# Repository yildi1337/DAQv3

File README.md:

# DAQv3
A Dual-Channel, Low Noise, Modular, 100 kHz Bandwidth, 24-Bit Data Acquisition (DAQ) Device / FFT Signal Analyzer

# Table of Contents

- **[Introduction](#introduction)**
- **[CAD Model](#cad-model)**
- **[Modules](#modules)**
  - [AnalogConversion_v1](#AnalogConversion_v1)
  - [AnalogConversion_v2](#AnalogConversion_v2)
  - [AnalogConversion_v3](#AnalogConversion_v3)
  - [Backplane_v1](#Backplane_v1)
  - [DigitalBackend_v1](#DigitalBackend_v1)
  - [PowerSupply_5V_v1](#PowerSupply_5V_v1)
  - [PowerSupply_5V_v2](#PowerSupply_5V_v2)
  - [PowerSupply_12V_v1](#PowerSupply_12V_v1)
  - [PowerSupply_12V_v2](#PowerSupply_12V_v2)
  - [USBConnectors_v1](#USBConnectors_v1)
- **[Firmware](#firmware)**
- **[USB Driver](#usb-driver)**
- **[Debug and Control Interface](#debug-and-control-interface)**
- **[Measurement Results](#measurement-results)**
  - [Linear Power Supply vs. Switched-Mode Power Supply](#linear-power-supply-vs-switched-mode-power-supply)
  - [Differential Input Module (AnalogConversion_v3)](#differential-input-module-analogconversion_v3)

# Introduction

Work in progress ...

# Rack
+ [Card Rail](https://it.rs-online.com/web/p/montanti-rack/2457848)
+ [Front Pannel Large](https://it.rs-online.com/web/p/accessori-per-contenitori/2879769) (10 HP)
+ [Front Pannel Small](https://us.rs-online.com/product/nvent-schroff/20848664/70294016/)  (4 HP)
+ [Case](https://it.rs-online.com/web/p/contenitori-e-scatole-rack/2550700?searchId=d65bfb2c-882b-444f-99ba-9c0d112e01d9&gb=s)  (42 HP)
+ [IEC Connector](https://it.rs-online.com/web/p/filtri-iec/8703669)

# CAD Model

The complete CAD model can be downloaded <a href="https://github.com/yildi1337/DAQv3/tree/main/cad_complete/inventor">here</a> (Autodesk Inventor 2023 files) including all <a href="#modules">modules</a> and the case.

# Modules

## AnalogConversion_v1

- [Schematics (PDF)](https://github.com/yildi1337/DAQv3/blob/main/schematics/AnalogConversion_v1_Schematics.pdf)
- [Schematics (Eagle)](https://github.com/yildi1337/DAQv3/blob/main/eagle/AnalogConversion_v1.sch)
- [Board (Eagle)](https://github.com/yildi1337/DAQv3/blob/main/eagle/AnalogConversion_v1.brd)
- [Gerber Files](https://github.com/yildi1337/DAQv3/blob/main/pcb_gerber/AnalogConversion_v1_2022-03-20.zip)
- [3D Step File](https://github.com/yildi1337/DAQv3/blob/main/cad_modules_step/AnalogConversion_v1.step)
- [Bill of Materials](https://github.com/yildi1337/DAQv3/blob/main/pcb_bom/BOM_AnalogConversion_v1.txt)

## AnalogConversion_v2

- [Schematics (PDF)](https://github.com/yildi1337/DAQv3/blob/main/schematics/AnalogConversion_v2_Schematics.pdf)
- [Schematics (Eagle)](https://github.com/yildi1337/DAQv3/blob/main/eagle/AnalogConversion_v2.sch)
- [Board (Eagle)](https://github.com/yildi1337/DAQv3/blob/main/eagle/AnalogConversion_v2.brd)
- [Gerber Files](https://github.com/yildi1337/DAQv3/blob/main/pcb_gerber/AnalogConversion_v2_2022-05-25.zip)
- [3D Step File](https://github.com/yildi1337/DAQv3/blob/main/cad_modules_step/AnalogConversion_v2.step)
- [Bill of Materials](https://github.com/yildi1337/DAQv3/blob/main/pcb_bom/BOM_AnalogConversion_v2.txt)

## AnalogConversion_v3

- [Schematics (PDF)](https://github.com/yildi1337/DAQv3/blob/main/schematics/AnalogConversion_v3_Schematics.pdf)
- [Schematics (Eagle)](https://github.com/yildi1337/DAQv3/blob/main/eagle/AnalogConversion_v3.sch)
- [Board (Eagle)](https://github.com/yildi1337/DAQv3/blob/main/eagle/AnalogConversion_v3.brd)
- [Gerber Files](https://github.com/yildi1337/DAQv3/blob/main/pcb_gerber/AnalogConversion_v3_2022-07-25.zip)
- [3D Step File](https://github.com/yildi1337/DAQv3/blob/main/cad_modules_step/AnalogConversion_v3.step)
- [Bill of Materials](https://github.com/yildi1337/DAQv3/blob/main/pcb_bom/BOM_AnalogConversion_v3.txt)

## Backplane_v1

- [Schematics (PDF)](https://github.com/yildi1337/DAQv3/blob/main/schematics/Backplane_v1_Schematics.pdf)
- [Schematics (Eagle)](https://github.com/yildi1337/DAQv3/blob/main/eagle/Backplane_v1.sch)
- [Board (Eagle)](https://github.com/yildi1337/DAQv3/blob/main/eagle/Backplane_v1.brd)
- [Gerber Files](https://github.com/yildi1337/DAQv3/blob/main/pcb_gerber/Backplane_v1_2022-03-20.zip)
- [3D Step File](https://github.com/yildi1337/DAQv3/blob/main/cad_modules_step/Backplane_v1.step)
- [Bill of Materials](https://github.com/yildi1337/DAQv3/blob/main/pcb_bom/BOM_Backplane_v1.txt)

## DigitalBackend_v1

- [Schematics (PDF)](https://github.com/yildi1337/DAQv3/blob/main/schematics/DigitalBackend_v1_Schematics.pdf)
- [Schematics (Eagle)](https://github.com/yildi1337/DAQv3/blob/main/eagle/DigitalBackend_v1.sch)
- [Board (Eagle)](https://github.com/yildi1337/DAQv3/blob/main/eagle/DigitalBackend_v1.brd)
- [Gerber Files](https://github.com/yildi1337/DAQv3/blob/main/pcb_gerber/DigitalBackend_v1_2022-03-20.zip)
- [3D Step File](https://github.com/yildi1337/DAQv3/blob/main/cad_modules_step/DigitalBackend_v1.step)
- [Bill of Materials](https://github.com/yildi1337/DAQv3/blob/main/pcb_bom/BOM_DigitalBackend_v1.txt)

## PowerSupply_12V_v1

- [Schematics (PDF)](https://github.com/yildi1337/DAQv3/blob/main/schematics/PowerSupply_12V_v1_Schematics.pdf)
- [Schematics (Eagle)](https://github.com/yildi1337/DAQv3/blob/main/eagle/PowerSupply_12V_v1.sch)
- [Board (Eagle)](https://github.com/yildi1337/DAQv3/blob/main/eagle/PowerSupply_12V_v1.brd)
- [Gerber Files](https://github.com/yildi1337/DAQv3/blob/main/pcb_gerber/PowerSupply_12V_v1_2022-03-20.zip)
- [3D Step File](https://github.com/yildi1337/DAQv3/blob/main/cad_modules_step/PowerSupply_12V_v1.step)
- [Bill of Materials](https://github.com/yildi1337/DAQv3/blob/main/pcb_bom/BOM_PowerSupply_12V_v1.txt)

## PowerSupply_12V_v2

- [Schematics (PDF)](https://github.com/yildi1337/DAQv3/blob/main/schematics/PowerSupply_12V_v2_Schematics.pdf)
- [Schematics (Eagle)](https://github.com/yildi1337/DAQv3/blob/main/eagle/PowerSupply_12V_v2.sch)
- [Board (Eagle)](https://github.com/yildi1337/DAQv3/blob/main/eagle/PowerSupply_12V_v2.brd)
- [Gerber Files](https://github.com/yildi1337/DAQv3/blob/main/pcb_gerber/PowerSupply_12V_v2_2022-05-25.zip)
- [3D Step File](https://github.com/yildi1337/DAQv3/blob/main/cad_modules_step/PowerSupply_12V_v2.step)
- [Bill of Materials](https://github.com/yildi1337/DAQv3/blob/main/pcb_bom/BOM_PowerSupply_12V_v2.txt)

## PowerSupply_5V_v1

- [Schematics (PDF)](https://github.com/yildi1337/DAQv3/blob/main/schematics/PowerSupply_5V_v1_Schematics.pdf)
- [Schematics (Eagle)](https://github.com/yildi1337/DAQv3/blob/main/eagle/PowerSupply_5V_v1.sch)
- [Board (Eagle)](https://github.com/yildi1337/DAQv3/blob/main/eagle/PowerSupply_5V_v1.brd)
- [Gerber Files](https://github.com/yildi1337/DAQv3/blob/main/pcb_gerber/PowerSupply_5V_v1_2022-03-20.zip)
- [3D Step File](https://github.com/yildi1337/DAQv3/blob/main/cad_modules_step/PowerSupply_5V_v1.step)
- [Bill of Materials](https://github.com/yildi1337/DAQv3/blob/main/pcb_bom/BOM_PowerSupply_5V_v1.txt)

## PowerSupply_5V_v2

- [Schematics (PDF)](https://github.com/yildi1337/DAQv3/blob/main/schematics/PowerSupply_5V_v2_Schematics.pdf)
- [Schematics (Eagle)](https://github.com/yildi1337/DAQv3/blob/main/eagle/PowerSupply_5V_v2.sch)
- [Board (Eagle)](https://github.com/yildi1337/DAQv3/blob/main/eagle/PowerSupply_5V_v2.brd)
- [Gerber Files](https://github.com/yildi1337/DAQv3/blob/main/pcb_gerber/PowerSupply_5V_v2_2022-05-25.zip)
- [3D Step File](https://github.com/yildi1337/DAQv3/blob/main/cad_modules_step/PowerSupply_5V_v2.step)
- [Bill of Materials](https://github.com/yildi1337/DAQv3/blob/main/pcb_bom/BOM_PowerSupply_5V_v2.txt)

## USBConnectors_v1

- [Schematics (PDF)](https://github.com/yildi1337/DAQv3/blob/main/schematics/USBConnectors_v1_Schematics.pdf)
- [Schematics (Eagle)](https://github.com/yildi1337/DAQv3/blob/main/eagle/USBConnectors_v1.sch)
- [Board (Eagle)](https://github.com/yildi1337/DAQv3/blob/main/eagle/USBConnectors_v1.brd)
- [Gerber Files](https://github.com/yildi1337/DAQv3/blob/main/pcb_gerber/USBConnectors_v1_2022-03-14.zip)
- [3D Step File](https://github.com/yildi1337/DAQv3/blob/main/cad_modules_step/USBConnectors_v1.step)
- [Bill of Materials](https://github.com/yildi1337/DAQv3/blob/main/pcb_bom/BOM_USBConnectors_v1.txt)

# Firmware

The firmware running on the STM32H753ZIT6 is mainly written in ANSI C and has been developed in <a href="https://www.st.com/en/development-tools/stm32cubeide.html">STM32CubeIDE</a> version 1.10.1 utilizing the official <a href="https://github.com/STMicroelectronics/stm32h7xx_hal_driver">STM32H7xx_HAL_Driver</a>. Among others, the firmware performs the following tasks:

- Configuration of the ADC AD7768 (on module <a href="#AnalogConversion_v3">AnalogConversion_v3</a>) via SPI (SPI_3).
- Reception of sampled data from the ADC AD7768 via SPI (SPI_2) and DMA (DMA1_Stream0).
- Transmission of sampled data from the ADC AD7768 via USB 2.0 Hi-Speed to the PC utilizing ULPI interface and an additional Hi-Speed USB PHY (USB3300).
- Handling USART connection (USART_1, via FT232RL chip on <a href="#USBConnectors_v1">USBConnectors_v1</a>) for debug purposes and for exchanging control/status commands with the PC.
- Controlling I2C bus (I2C_4) for controlling I/O expander TCA9534A (e.g. on module <a href="#AnalogConversion_v3">AnalogConversion_v3</a>) which, in turn, drives a relay driver (MAX4820) on the same module.
- Controlling front LEDs (on module <a href="#DigitalBackend_v1">DigitalBackend_v1</a>).

The complete source code can be found <a href="https://github.com/yildi1337/DAQv3/tree/main/firmware">here</a>.

# USB Driver

Two USB drivers are needed for operating the DAQ v3:

- For the reception of the sampled data from the ADC NI-VISA is utilized. The driver matching the hardware of this project has been generated with the NI-VISA Driver Wizard an can be downloaded <a href="https://github.com/yildi1337/DAQv3/tree/main/usb_driver/ni-visa">here</a>.
- To use the USB debug interface only the official USB serial driver from FTDI is required, which can be downloaded <a href="https://github.com/yildi1337/DAQv3/tree/main/usb_driver/ftdi">here</a>.

# Debug and Control Interface

Tool for graphical display of status information and for controlling the hardware via the virtual serial interface (second USB-B port). The python source code and a binary (only tested on x64 Microsoft Windows 10) can be downloaded <a href="https://github.com/yildi1337/DAQv3/tree/main/debug_interface">here</a>. 

# Measurement Results

## Linear Power Supply vs. Switched-Mode Power Supply

Noise measurements (60 seconds) were performed while powering the electronics with the power supplies of versions v1 and v2, where the abbreviations PS and ACNV in the titles refer to the power supply and analog conversion modules.

The two linear power supply modules of version v1 both operate with transformers. This resulted in heavy magnetic interference in the form of the mains frequency and multiples thereof.

The two power supply modules of version v2 both operate with AC/DC power modules (<a href="https://www.tracopower.com/de/deu/model/tmlm-20105">TMLM 20105</a>, <a href="https://www.tracopower.com/de/deu/model/tmlm-20115">TMLM 20115</a>) from Traco Power. Their switching frequencies are around 132 +/- 8 kHz and thus above the useful range of 0 - 100 kHz (Nyquist frequency is 128 kHz).

## Differential Input Module (AnalogConversion_v3)

The investigated setup consists of the modules:

- <a href="#Backplane_v1">Backplane_v1</a>
- <a href="#PowerSupply_5V_v2">PowerSupply_5V_v2</a>
- <a href="#PowerSupply_12V_v2">PowerSupply_12V_v2</a>
- <a href="#AnalogConversion_v3">AnalogConversion_v3</a>
- <a href="#DigitalBackend_v1">DigitalBackend_v1</a>
- <a href="#USBConnectors_v1">USBConnectors_v1</a>

### Mains Interference and Grounding

The two differential inputs of each channel were connected via <a href="https://www.mouser.de/ProductDetail/Amphenol-RF/132360?qs=V8V9vCxO5JtDrelx3RqrVA%3D%3D">50 Ohm SMA resistors</a> with AGND (SHIELD connected via R6 = 0 Ohm with AGND, <a href="https://github.com/yildi1337/DAQv3/blob/main/schematics/AnalogConversion_v3_Schematics.pdf">see schematics</a>).

Obviously, the lowest interference occurs in grounded mode and when GND of the backplane is directly connected to the chassis/the protective earth connector of the power entry module (first plot).

### Input Noise of Differential Opamp Driver and ADC

The measurement result from above is essential for the further development of the preamplifier. The gain of the preamplifier must be high enough to be able to neglect the noise from the opamp driver (ADA4945-1) and ADC (AD7768-4) determined here. A useful model for describing the power spectral density of the voltage noise $PSD(f)$ (in units of $\mathrm{V}^2/\mathrm{Hz}$) is the polynomial law 
$$\mathrm{PSD}(f) = \mathrm{LSD}^2(f) = \sum_{i=-1}^{0} b_i f^i$$ 
where $i=0$ and $i=-1$ refer to white noise and $1/f$ flicker noise, respectively, and $\mathrm{LSD}(f)$ referes to the linear spectrum density (in units of $\mathrm{V}/\sqrt{\mathrm{Hz}}$). For this measurement, values of
- $b_{-1} = 1.3 \cdot 10^{-13}~\mathrm{V}^2$
- $b_0 = {1.3 \cdot 10^{-15}~\mathrm{V}^2/\mathrm{Hz}}$
were found.

This results in a $1/f$ corner frequency of $f_{\mathrm{c}} = b_{-1}/b_0 = 100~\mathrm{Hz}$. The white voltage noise density is equal to $\sqrt{b_0} = 36~\mathrm{nV}/\sqrt{\mathrm{Hz}}$. Based on the two time domain noise signals RMS noise values of $13.2~\mu\mathrm{V}$ (channel 1) and $13.5~\mu\mathrm{V}$ (channel 2) were determined after substracting the DC offsets of $-6.5~\mathrm{mV}$ and $-1.8~\mathrm{mV}$.

The measured RMS noise values are in good agreement with the value of $11.58~\mu\mathrm{V}$ given in the datasheet (for the ADC only).

In addition, for $V_{\mathrm{ref}} = 5~\mathrm{V}$, the dynamic range of the utilized combination of opamp driver and ADC is better than 

$$\mathrm{DR} = 20 \cdot \log_{10}\left(\frac{2 \cdot V_{\mathrm{ref}}}{\sqrt{2} \cdot \mathrm{RMS}\ \mathrm{noise}}\right)~\mathrm{dB} = 114\ \mathrm{dB}$$ 

### ADC RAW Data for Several Input Configurations

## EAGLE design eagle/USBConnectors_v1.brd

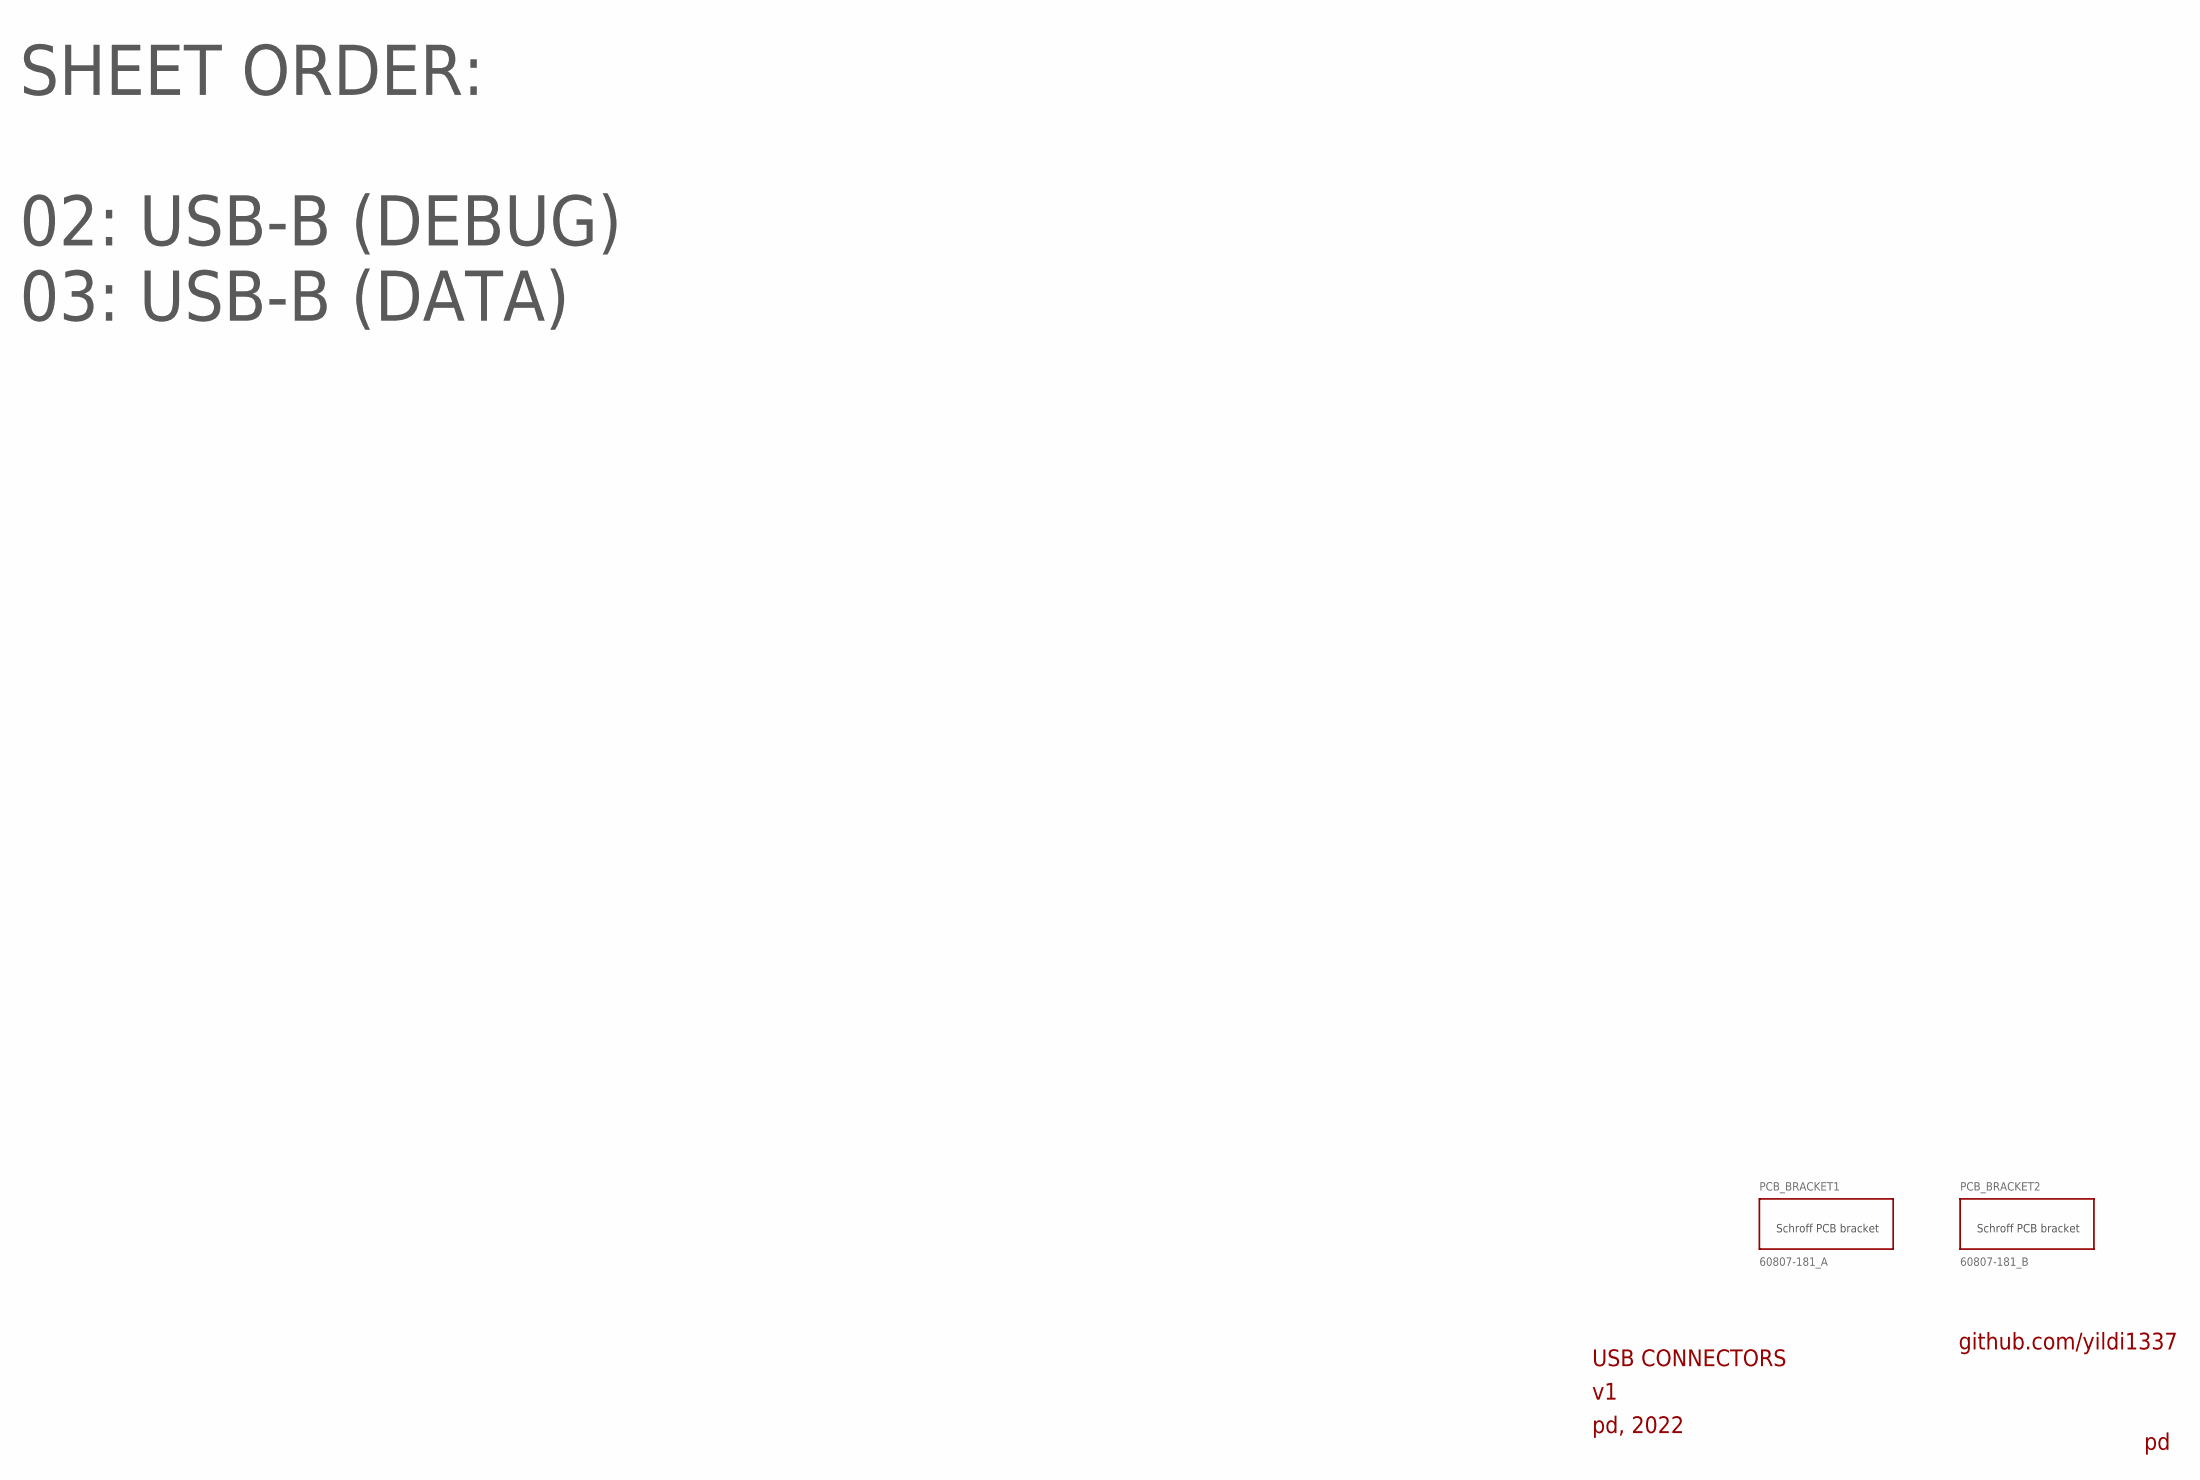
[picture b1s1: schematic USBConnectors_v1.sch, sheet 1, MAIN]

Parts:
PCB_BRACKET1: 60807-181_A
PCB_BRACKET2: 60807-181_B

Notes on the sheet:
USB CONNECTORS
pd, 2022
github.com/yildi1337
SHEET ORDER: 02: USB-B (DEBUG) 03: USB-B (DATA)

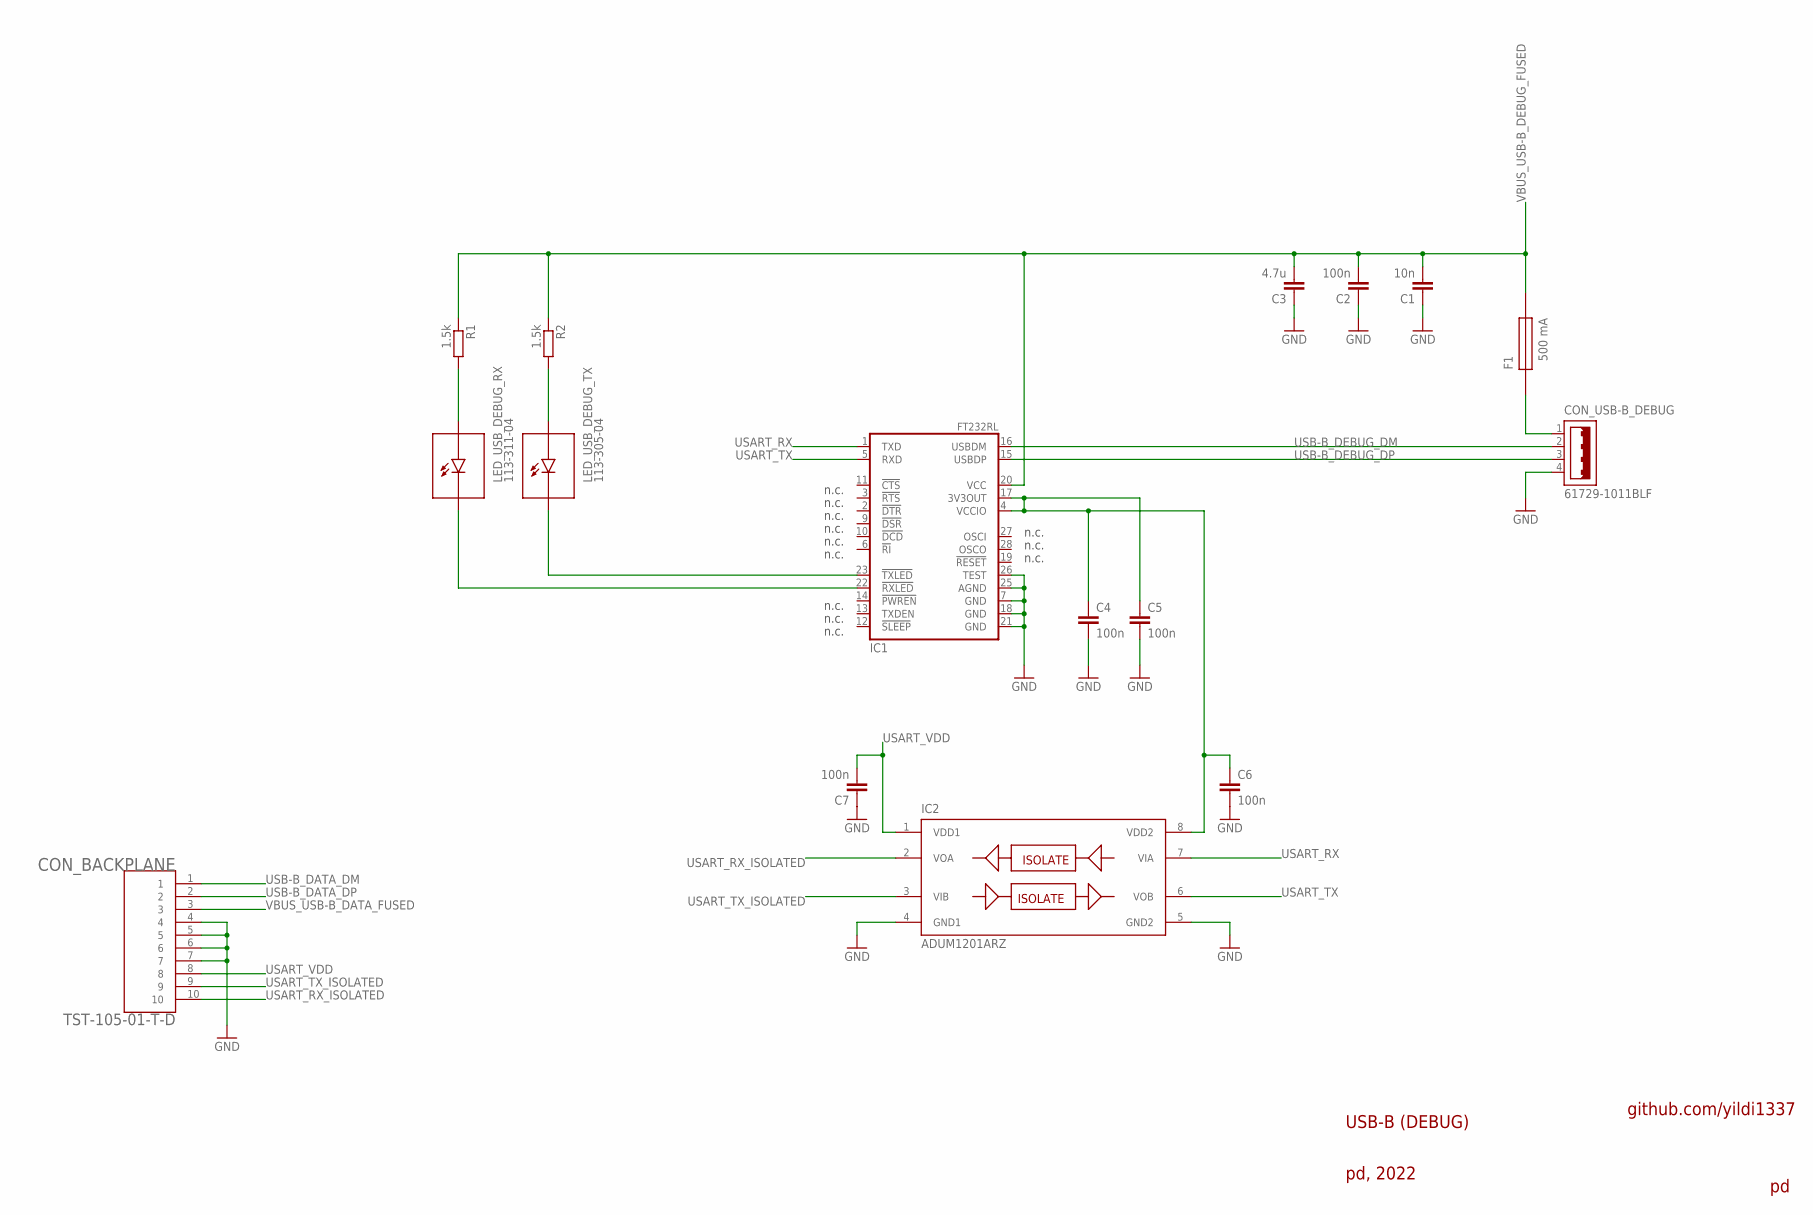
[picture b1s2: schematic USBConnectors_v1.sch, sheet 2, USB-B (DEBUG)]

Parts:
C1: 10n; C0603
C2, C4, C5, C6, C7: 100n; C0603
C3: 4.7u; C0603
CON_BACKPLANE: TST-105-01-T-D
CON_USB-B_DEBUG: 61729-1011BLF
F1: 500 mA; LITTELFUSE_466_SERIES
IC1: FT232RL
IC2: ADUM1201ARZ; SO8
LED_USB_DEBUG_RX: 113-311-04
LED_USB_DEBUG_TX: 113-305-04
R1, R2: 1.5k; R0603

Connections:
GND: C1.2, C2.1, C3.1, C4.2, C5.2, C6.2, C7.1, CON_BACKPLANE.4, CON_BACKPLANE.5, CON_BACKPLANE.6, CON_BACKPLANE.7, CON_USB-B_DEBUG.4, IC1.7 (GND), IC1.18 (GND), IC1.21 (GND), IC1.25 (AGND), IC1.26 (TEST), IC2.4 (GND1), IC2.5 (GND2); also elsewhere on the board
unnamed: CON_USB-B_DEBUG.1, F1.1
unnamed: LED_USB_DEBUG_RX.+ (A), R1.2
unnamed: LED_USB_DEBUG_TX.+ (A), R2.2
unnamed: C4.1, C5.1, C6.1, IC1.4 (VCCIO), IC1.17 (3V3OUT), IC2.8 (VDD2)
unnamed: IC1.22 (!RXLED), LED_USB_DEBUG_RX.- (C)
unnamed: IC1.23 (!TXLED), LED_USB_DEBUG_TX.- (C)
USART_RX: IC1.1 (TXD), IC2.7 (VIA)
USART_RX_ISOLATED: CON_BACKPLANE.10, IC2.2 (VOA)
USART_TX: IC1.5 (RXD), IC2.6 (VOB)
USART_TX_ISOLATED: CON_BACKPLANE.9, IC2.3 (VIB)
USART_VDD: C7.2, CON_BACKPLANE.8, IC2.1 (VDD1)
USB-B_DATA_DM: CON_BACKPLANE.1; also elsewhere on the board
USB-B_DATA_DP: CON_BACKPLANE.2; also elsewhere on the board
USB-B_DEBUG_DM: CON_USB-B_DEBUG.2, IC1.16 (USBDM)
USB-B_DEBUG_DP: CON_USB-B_DEBUG.3, IC1.15 (USBDP)
VBUS_USB-B_DATA_FUSED: CON_BACKPLANE.3; also elsewhere on the board
VBUS_USB-B_DEBUG_FUSED: C1.1, C2.2, C3.2, F1.2, IC1.20 (VCC), R1.1, R2.1

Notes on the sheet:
n.c.
USB-B (DEBUG)
pd, 2022
github.com/yildi1337

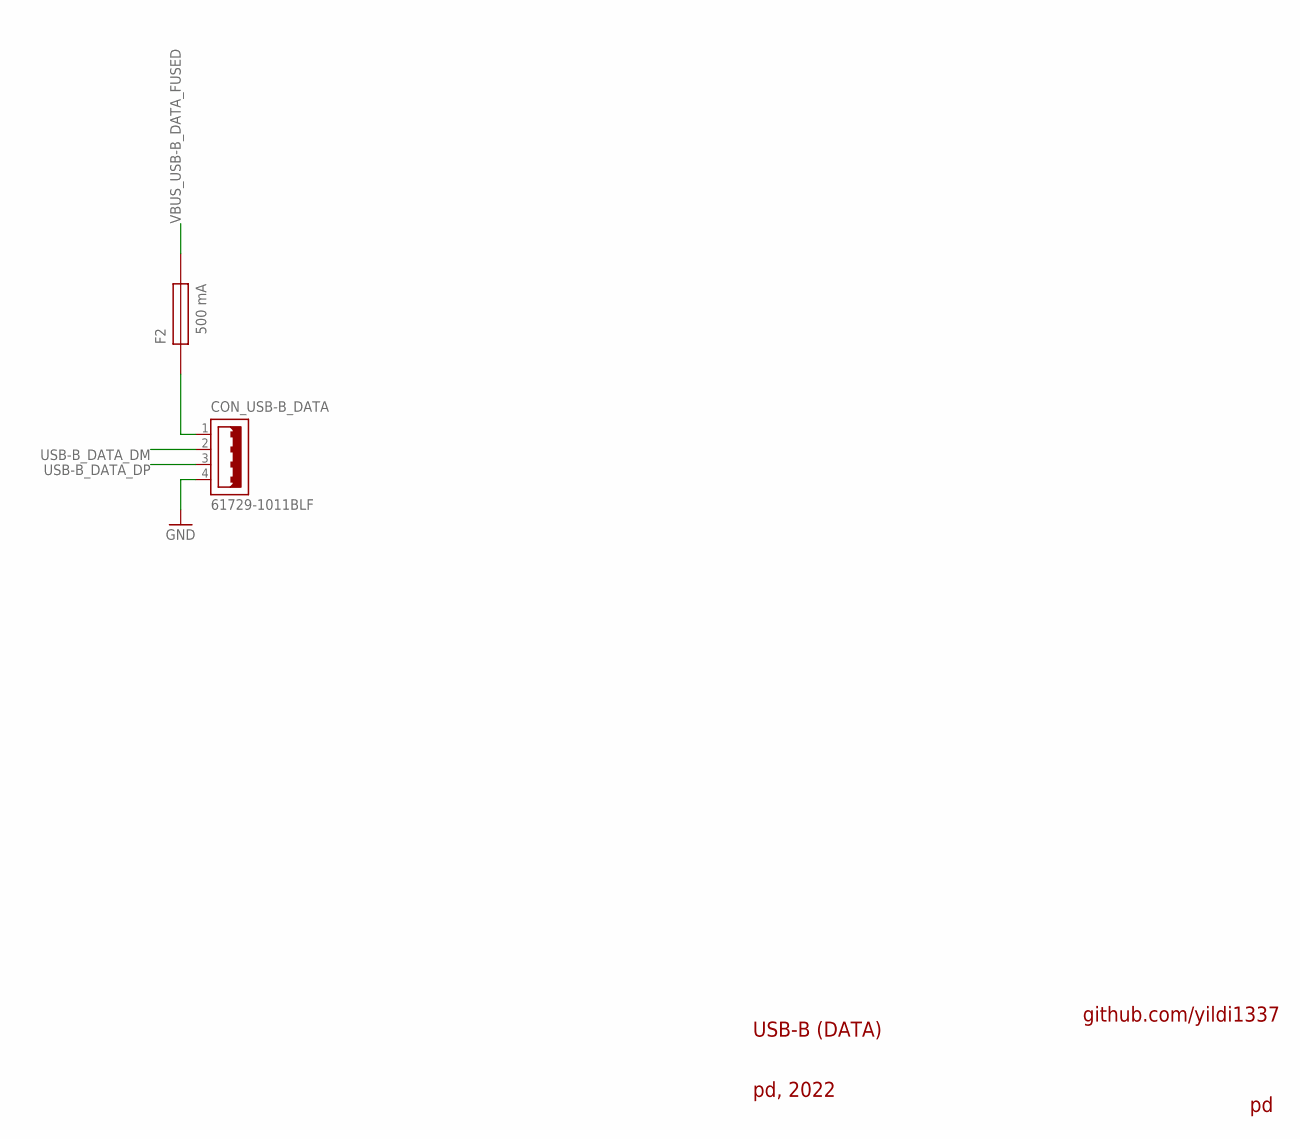
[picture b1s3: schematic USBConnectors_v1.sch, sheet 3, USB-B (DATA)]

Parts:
CON_USB-B_DATA: 61729-1011BLF
F2: 500 mA; LITTELFUSE_466_SERIES

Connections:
GND: CON_USB-B_DATA.4; also elsewhere on the board
USB-B_DATA_DM: CON_USB-B_DATA.2; also elsewhere on the board
USB-B_DATA_DP: CON_USB-B_DATA.3; also elsewhere on the board
VBUS_USB-B_DATA_FUSED: F2.2; also elsewhere on the board
VBUS_USB-B_NF: CON_USB-B_DATA.1, F2.1

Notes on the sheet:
USB-B (DATA)
pd, 2022
github.com/yildi1337

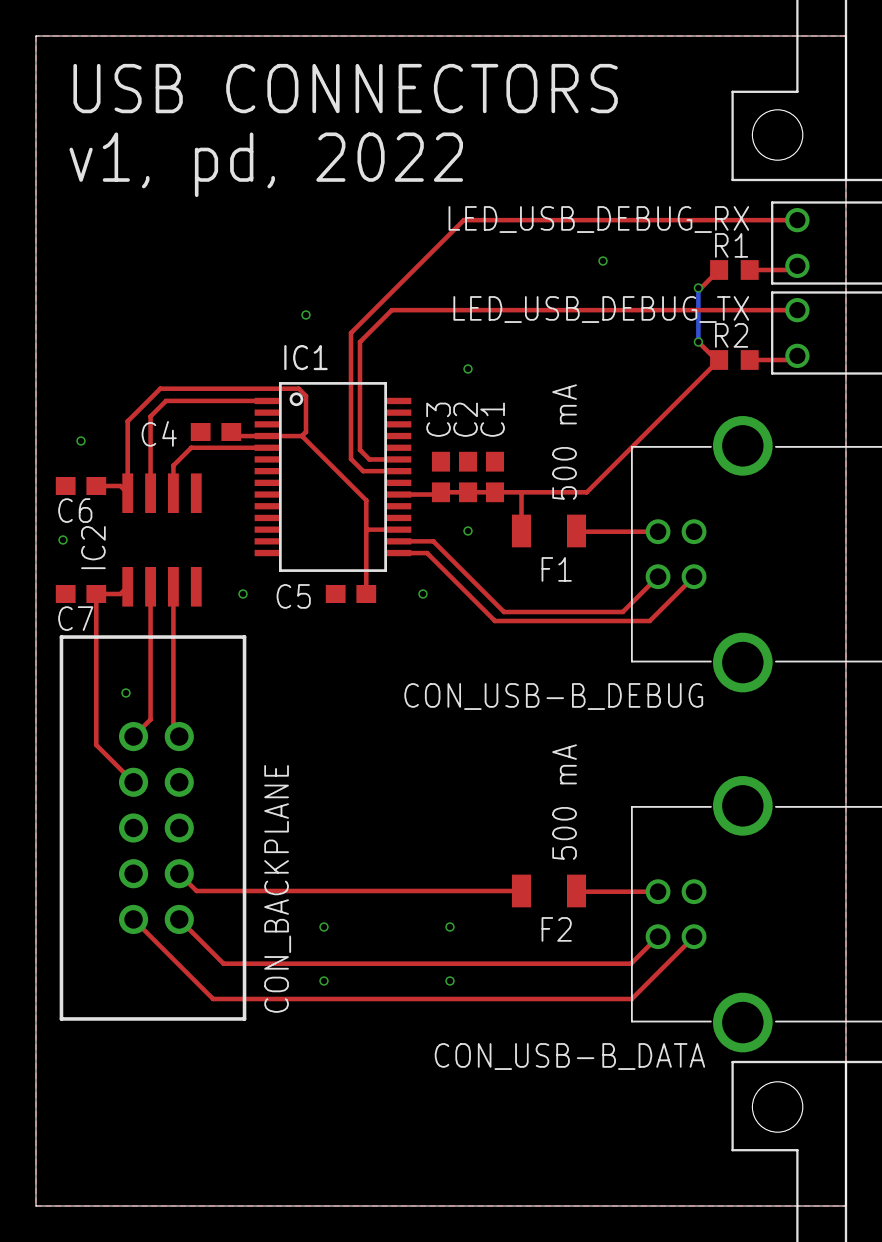
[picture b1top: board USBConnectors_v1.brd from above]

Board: 2 copper layers, 45.0 x 65.0 mm, 20 parts (0 on the bottom side), 19 nets.

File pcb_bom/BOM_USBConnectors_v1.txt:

Stückliste exportiert aus D:/OneDrive/Elektronikprojekte/DAQ v3 STM32H7/Eagle/USB Connectors v1/USBConnectors_v1.sch am 14.03.2022 20:18

Qty Value          Device                Package               Parts                           Description                POPULARITY SPICEPREFIX
2   1.5k           R-EU_R0603            R0603                 R1, R2                          RESISTOR, European symbol  70         R          
5   100n           C-EUC0603             C0603                 C2, C4, C5, C6, C7              CAPACITOR, European symbol 73         C          
1   10n            C-EUC0603             C0603                 C1                              CAPACITOR, European symbol 73         C          
1   113-305-04     113-305-04            113-305-04            LED_USB_DEBUG_TX                                                                 
1   113-311-04     113-311-04            113-311-04            LED_USB_DEBUG_RX                                                                 
1   4.7u           C-EUC0603             C0603                 C3                              CAPACITOR, European symbol 73         C          
2   500 mA         LITTELFUSE_466_SERIES LITTELFUSE_466_SERIES F1, F2                                                                           
1   60807-181_A    60807-181_A           60807-181_A           PCB_BRACKET1                                                                     
1   60807-181_B    60807-181_B           60807-181_B           PCB_BRACKET2                                                                     
2   61729-1011BLF  61729-1011BLF         61729-1011BLF         CON_USB-B_DATA, CON_USB-B_DEBUG                                                  
1   ADUM1201ARZ    ADUM1201              SO8                   IC2                                                                              
1   FT232RL        FT232RL               FT232RL               IC1                                                                              
1   TST-105-01-T-D TST-105-01-T-D        TST-105-01-T-D        CON_BACKPLANE

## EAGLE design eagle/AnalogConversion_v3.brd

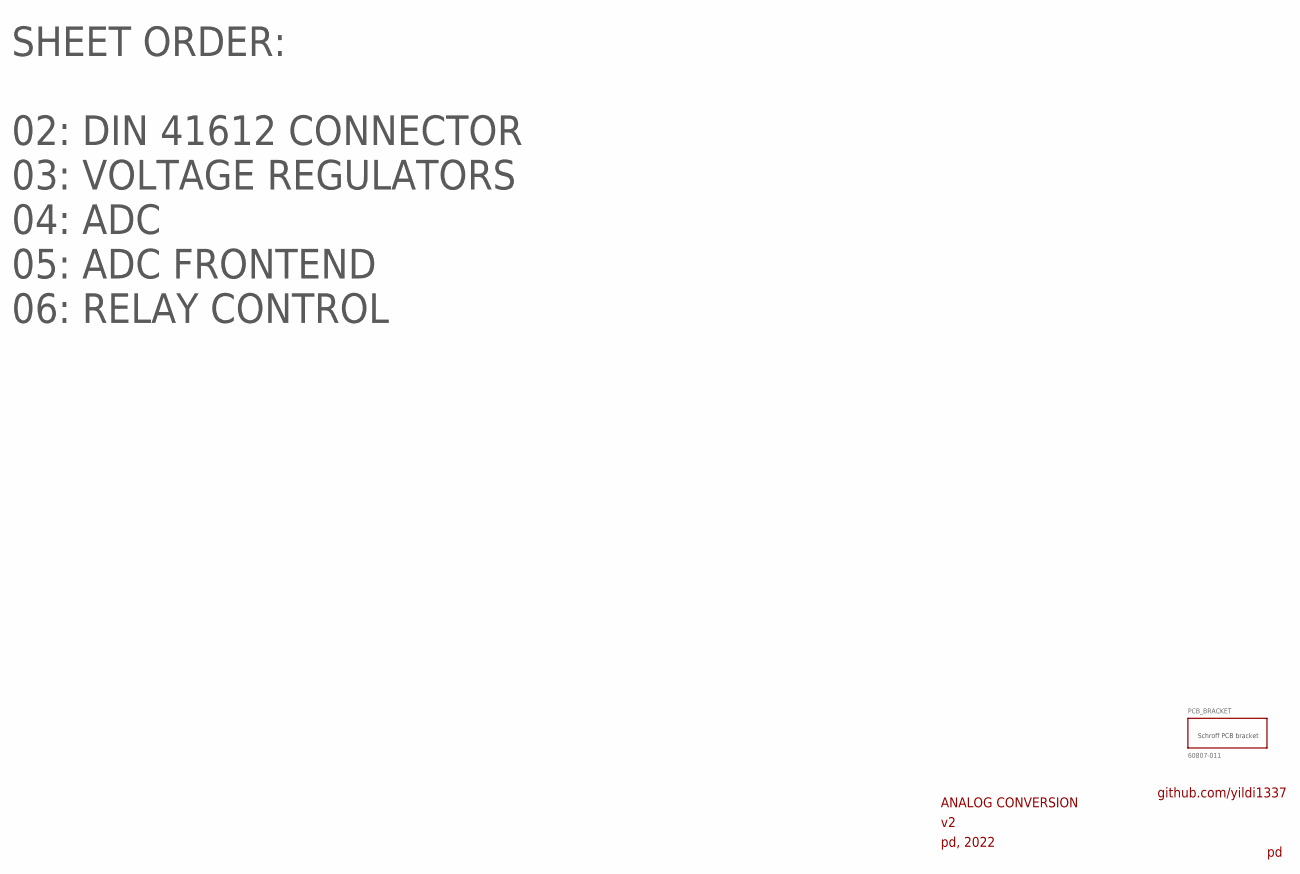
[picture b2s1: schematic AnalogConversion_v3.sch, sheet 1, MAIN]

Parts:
PCB_BRACKET: 60807-011

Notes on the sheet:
ANALOG CONVERSION
pd, 2022
github.com/yildi1337
SHEET ORDER: 02: DIN 41612 CONNECTOR 03: VOLTAGE REGULATORS 04: ADC 05: ADC FRONTEND 06: RELAY CONTROL

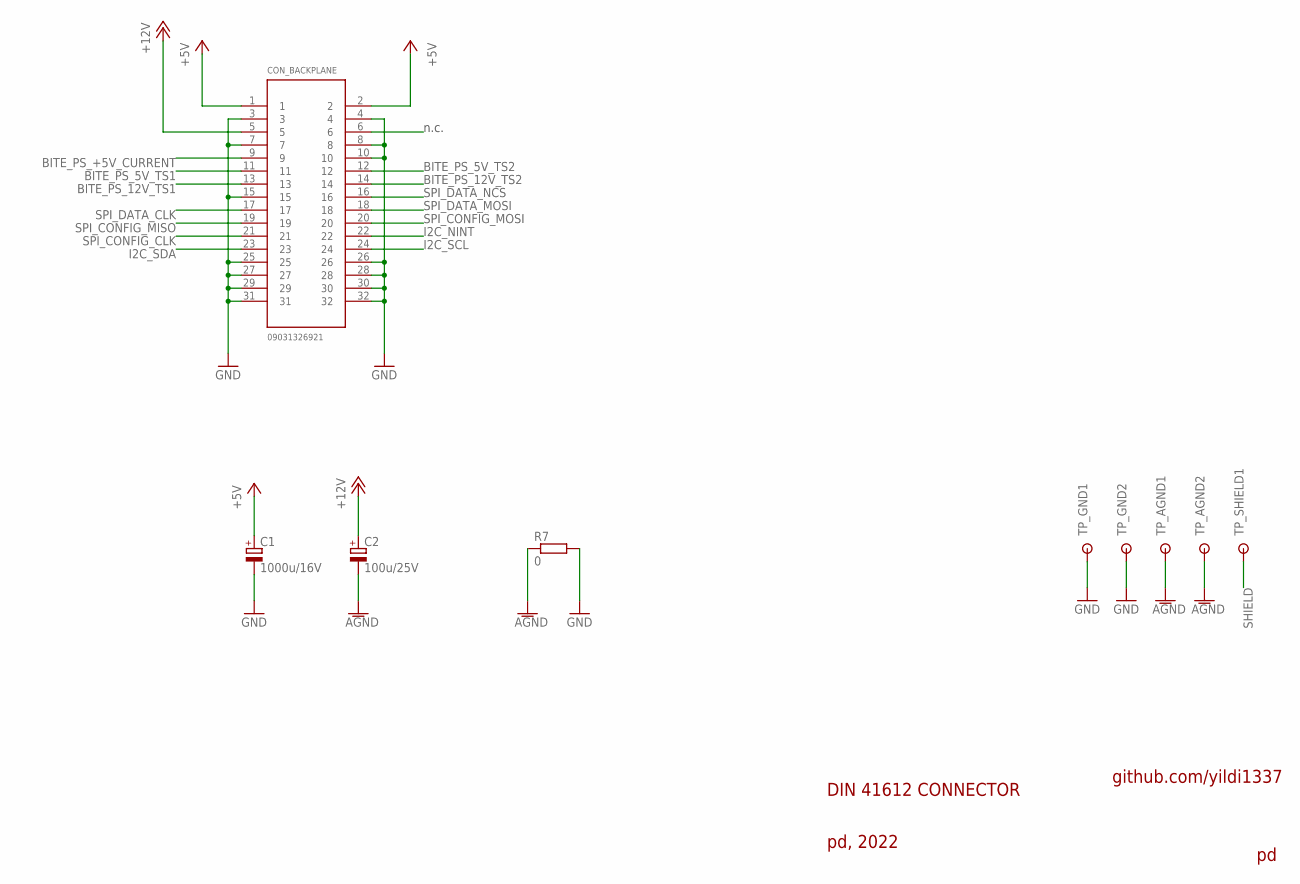
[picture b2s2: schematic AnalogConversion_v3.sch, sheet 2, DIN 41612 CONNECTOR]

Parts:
C1: 1000u/16V; 153CLV-1010
C2: 100u/25V; 153CLV-0810
CON_BACKPLANE: 09031326921
R7: 0; R0603
TP_AGND1, TP_AGND2: RSPRO-1MM-TERMINAL-POST-2622034
TP_GND1, TP_GND2: RSPRO-1MM-TERMINAL-POST-2622034
TP_SHIELD1: RSPRO-1MM-TERMINAL-POST-2622034

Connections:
+5V: C1.+, CON_BACKPLANE.1, CON_BACKPLANE.2; also elsewhere on the board
+12V: C2.+, CON_BACKPLANE.5; also elsewhere on the board
AGND: C2.-, R7.1, TP_AGND1.P$1, TP_AGND2.P$1; also elsewhere on the board
BITE_PS_5V_TS1: CON_BACKPLANE.11
BITE_PS_5V_TS2: CON_BACKPLANE.12
BITE_PS_12V_TS1: CON_BACKPLANE.13
BITE_PS_12V_TS2: CON_BACKPLANE.14
BITE_PS_+5V_CURRENT: CON_BACKPLANE.9
GND: C1.-, CON_BACKPLANE.3, CON_BACKPLANE.4, CON_BACKPLANE.7, CON_BACKPLANE.8, CON_BACKPLANE.10, CON_BACKPLANE.15, CON_BACKPLANE.25, CON_BACKPLANE.26, CON_BACKPLANE.27, CON_BACKPLANE.28, CON_BACKPLANE.29, CON_BACKPLANE.30, CON_BACKPLANE.31, CON_BACKPLANE.32, R7.2, TP_GND1.P$1, TP_GND2.P$1; also elsewhere on the board
I2C_NINT: CON_BACKPLANE.22; also elsewhere on the board
I2C_SCL: CON_BACKPLANE.24; also elsewhere on the board
I2C_SDA: CON_BACKPLANE.23; also elsewhere on the board
SHIELD: TP_SHIELD1.P$1; also elsewhere on the board
SPI_CONFIG_CLK: CON_BACKPLANE.21; also elsewhere on the board
SPI_CONFIG_MISO: CON_BACKPLANE.19; also elsewhere on the board
SPI_CONFIG_MOSI: CON_BACKPLANE.20; also elsewhere on the board
SPI_DATA_CLK: CON_BACKPLANE.17; also elsewhere on the board
SPI_DATA_MOSI: CON_BACKPLANE.18; also elsewhere on the board
SPI_DATA_NCS: CON_BACKPLANE.16; also elsewhere on the board

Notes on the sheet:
DIN 41612 CONNECTOR
pd, 2022
github.com/yildi1337
n.c.

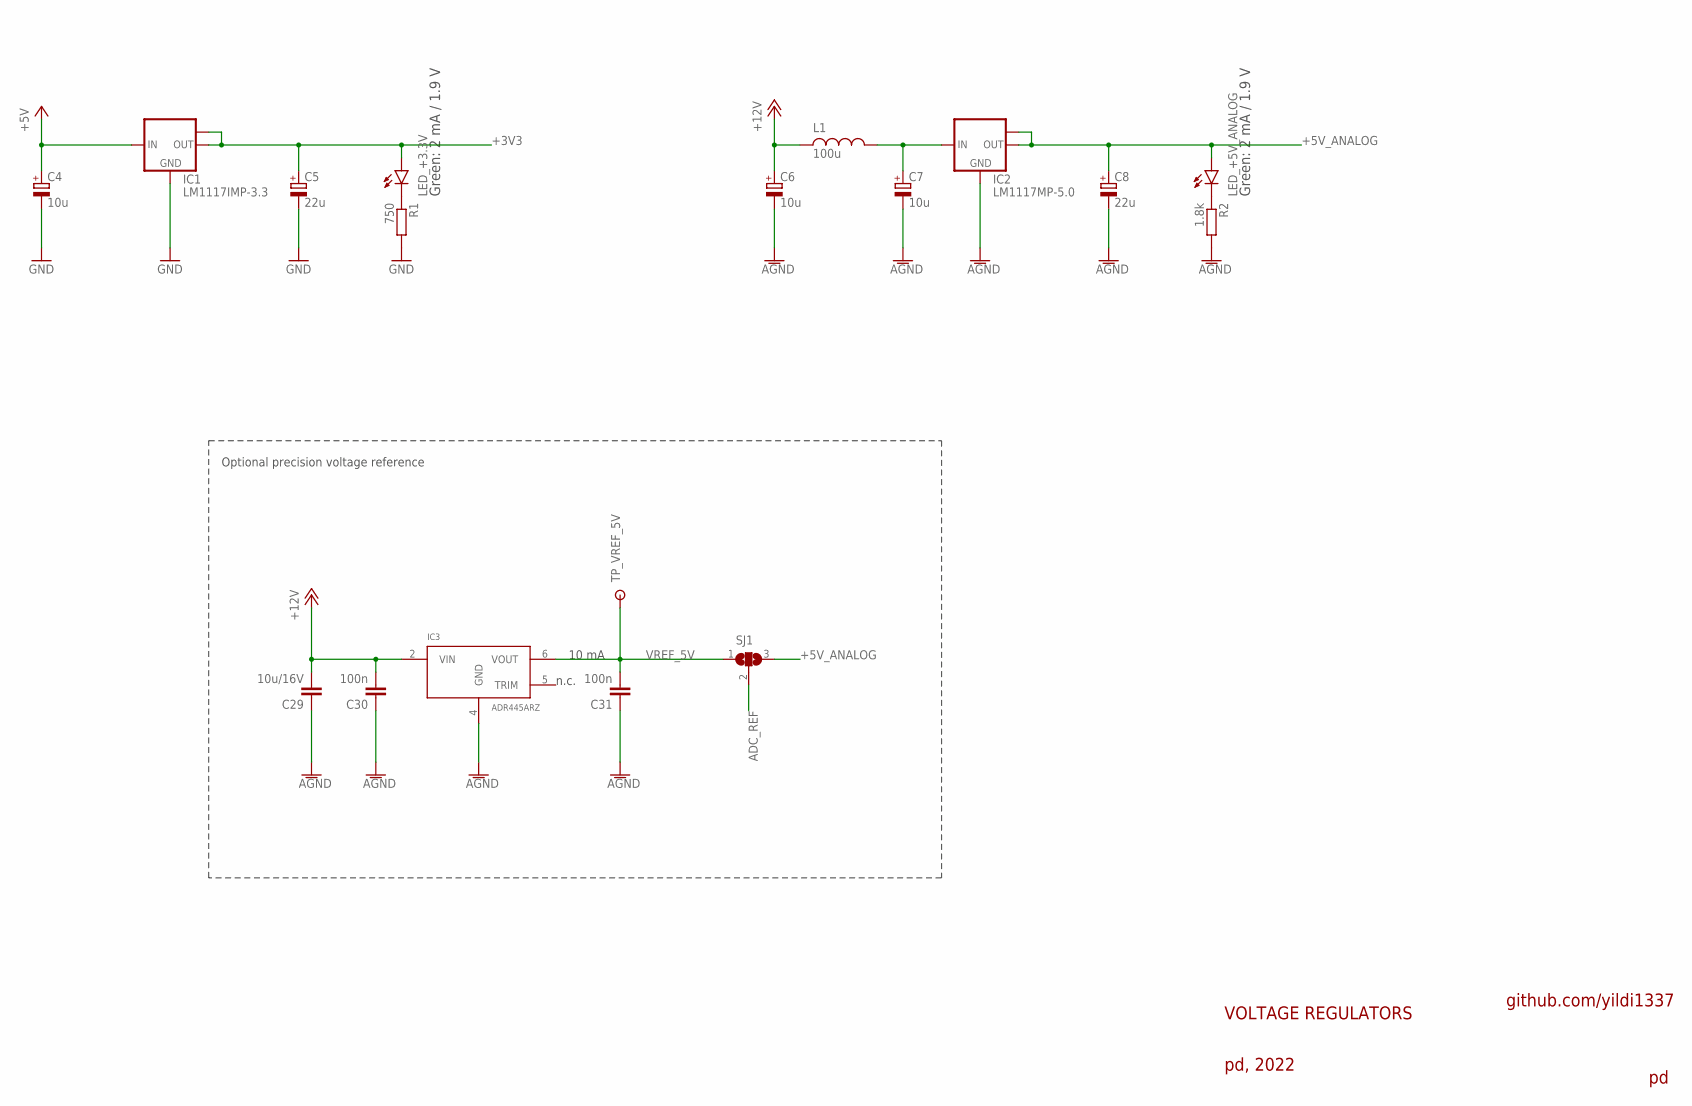
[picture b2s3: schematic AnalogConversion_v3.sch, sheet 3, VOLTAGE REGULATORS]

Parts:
C4, C6, C7: 10u; CT3216
C5, C8: 22u; CT6032
C29: 10u/16V; C0805
C30, C31: 100n; C0603
IC1: LM1117IMP-3.3; SOT223
IC2: LM1117MP-5.0; SOT223
IC3: ADR445ARZ
L1: 100u; VLS6045AF-101M
LED_+3.3V, LED_+5V_ANALOG: LEDCHIP-LED0603; CHIP-LED0603
R1: 750; R0603
R2: 1.8k; R0603
SJ1: SJ2W; SJ_2
TP_VREF_5V: RSPRO-1MM-TERMINAL-POST-2622034

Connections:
+3V3: C5.+, IC1.2 (OUT), IC1.TAB (OUT1), LED_+3.3V.A; also elsewhere on the board
+5V: C4.+, IC1.3 (IN); also elsewhere on the board
+5V_ANALOG: C8.+, IC2.2 (OUT), IC2.TAB (OUT1), LED_+5V_ANALOG.A, SJ1.3; also elsewhere on the board
+12V: C6.+, C29.2, C30.2, IC3.2 (VIN), L1.1; also elsewhere on the board
ADC_REF: SJ1.2; also elsewhere on the board
AGND: C6.-, C7.-, C8.-, C29.1, C30.1, C31.1, IC2.1 (GND), IC3.4 (GND), R2.2; also elsewhere on the board
GND: C4.-, C5.-, IC1.1 (GND), R1.2; also elsewhere on the board
unnamed: C7.+, IC2.3 (IN), L1.2
unnamed: LED_+3.3V.C, R1.1
unnamed: LED_+5V_ANALOG.C, R2.1
VREF_5V: C31.2, IC3.6 (VOUT), SJ1.1, TP_VREF_5V.P$1

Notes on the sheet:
VOLTAGE REGULATORS
pd, 2022
github.com/yildi1337
Green: 2 mA / 1.9 V
Optional precision voltage reference
10 mA
n.c.
